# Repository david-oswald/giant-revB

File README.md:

# GIAnt, the Generic Implementation ANalysis Toolkit

This is a fork of the original GIAnt project (www.sourceforge.net/projects/giant/) with a few changes.

## Changes

* The board
	* There is a GIAnt fault only design by David Oswald
	* The FPGA module is updated to `ZTEX USB-FPGA Module 2.04` with `series 2 to series 1 adapter board`

* The FPGA source code
	* Modified from `giant-20111116`
	* The FPGA selection of the project is changed to XC6SLX16
	* IP cores regenerated
	* .ucf file updated to match the new pinout of series 2 module

* The microcontroller source code is updated to fit the new board

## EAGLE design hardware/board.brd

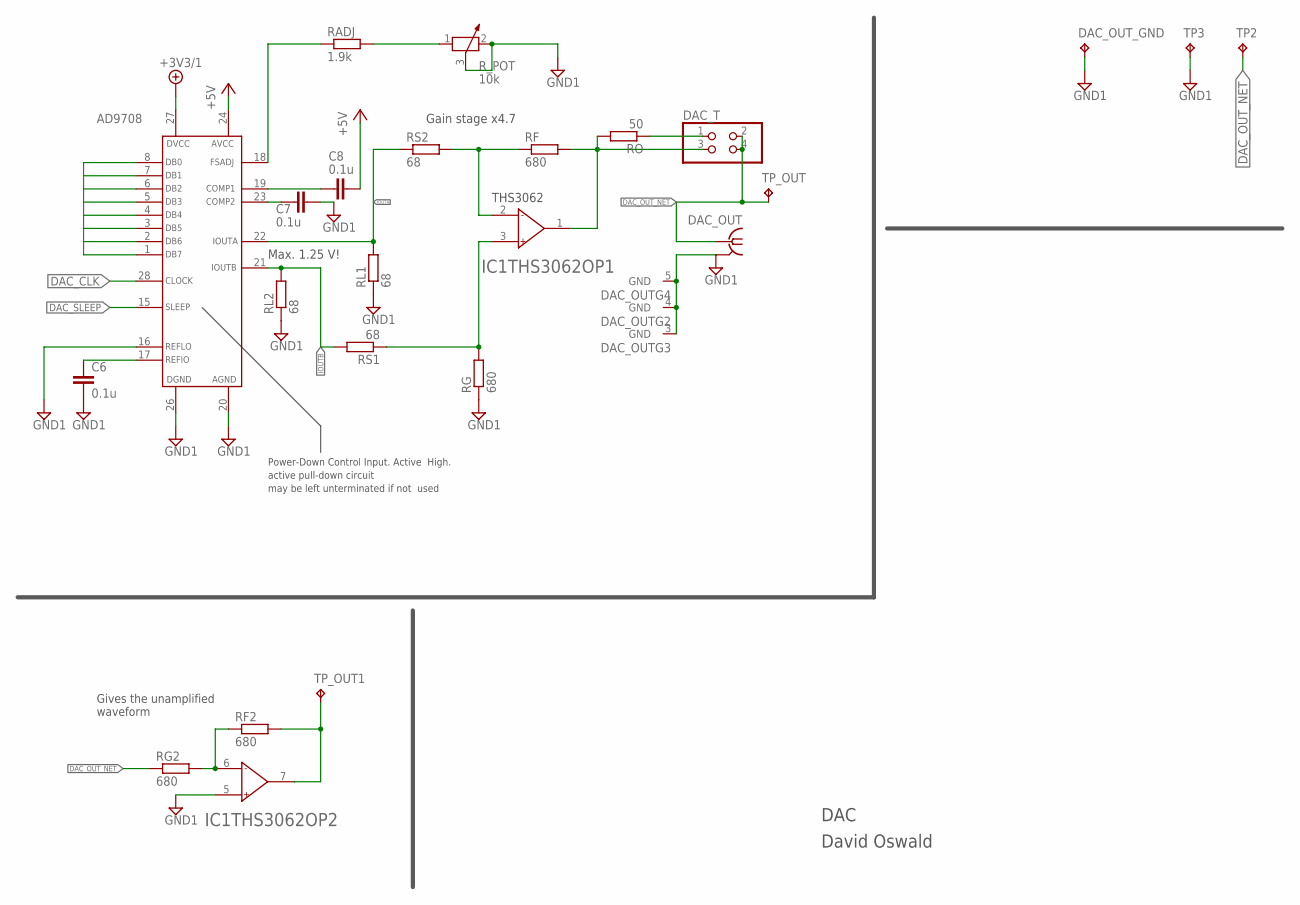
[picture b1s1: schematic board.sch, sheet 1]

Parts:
AD9708: AD7908; SO28W
C6, C7, C8: 0.1u; C0805K
DAC_OUT: BU-SMA-V
DAC_OUT_GND: TPB1,27; B1,27
DAC_T: PINHD-2X2; 2X02
IC1: THS3062; SO08
RADJ: 1.9k; R0805
RF, RF2: 680; R0805
RG, RG2: 680; R0805
RL1, RL2: 68; R0805
RO: 50; R0805
RS1, RS2: 68; R0805
R_POT: 10k; PT-SPIN
TP2, TP3: TPPAD1-13; P1-13
TP_OUT, TP_OUT1: TPB1,27; B1,27

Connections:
+5V: AD9708.24 (AVCC), C8.1; also elsewhere on the board
+5V/1: AD9708.27 (DVCC); also elsewhere on the board
COMP1: AD9708.19 (COMP1), C8.2
COMP2: AD9708.23 (COMP2), C7.1
DAC_CLK: AD9708.28 (CLOCK); also elsewhere on the board
DAC_OUT_NET: DAC_OUT.1, DAC_T.2, DAC_T.4, RG2.1, TP2.TP, TP_OUT.TP
DAC_SLEEP: AD9708.15 (SLEEP)
DB0: AD9708.8 (DB0); also elsewhere on the board
DB1: AD9708.7 (DB1); also elsewhere on the board
DB2: AD9708.6 (DB2); also elsewhere on the board
DB3: AD9708.5 (DB3); also elsewhere on the board
DB4: AD9708.4 (DB4); also elsewhere on the board
DB5: AD9708.3 (DB5); also elsewhere on the board
DB6: AD9708.2 (DB6); also elsewhere on the board
DB7: AD9708.1 (DB7); also elsewhere on the board
FSADJ: AD9708.18 (FSADJ), RADJ.1
GND1: AD9708.16 (REFLO), AD9708.20 (AGND), AD9708.26 (DGND), C6.2, C7.2, DAC_OUT.2 (GND), DAC_OUT.3 (GND), DAC_OUT.4 (GND), DAC_OUT.5 (GND), DAC_OUT_GND.TP, IC1.5 (IN+), RG.1, RL1.1, RL2.1, R_POT.2, R_POT.3, TP3.TP; also elsewhere on the board
IOUTA: AD9708.22 (IOUTA), RL1.2, RS2.1
IOUTB: AD9708.21 (IOUTB), RL2.2, RS1.2
unnamed: IC1.3 (IN+), RG.2, RS1.1
unnamed: IC1.2 (IN-), RF.1, RS2.2
unnamed: DAC_T.3, IC1.1 (OUT), RF.2, RO.2
unnamed: DAC_T.1, RO.1
unnamed: RADJ.2, R_POT.1
unnamed: IC1.6 (IN-), RF2.1, RG2.2
unnamed: IC1.7 (OUT), RF2.2, TP_OUT1.TP
REFIO: AD9708.17 (REFIO), C6.1

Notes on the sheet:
David Oswald
DAC
Max. 1.25 V!
Gain stage x4.7
Power-Down Control Input. Active High.
active pull-down circuit
may be left unterminated if not used
THS3062
Gives the unamplified waveform

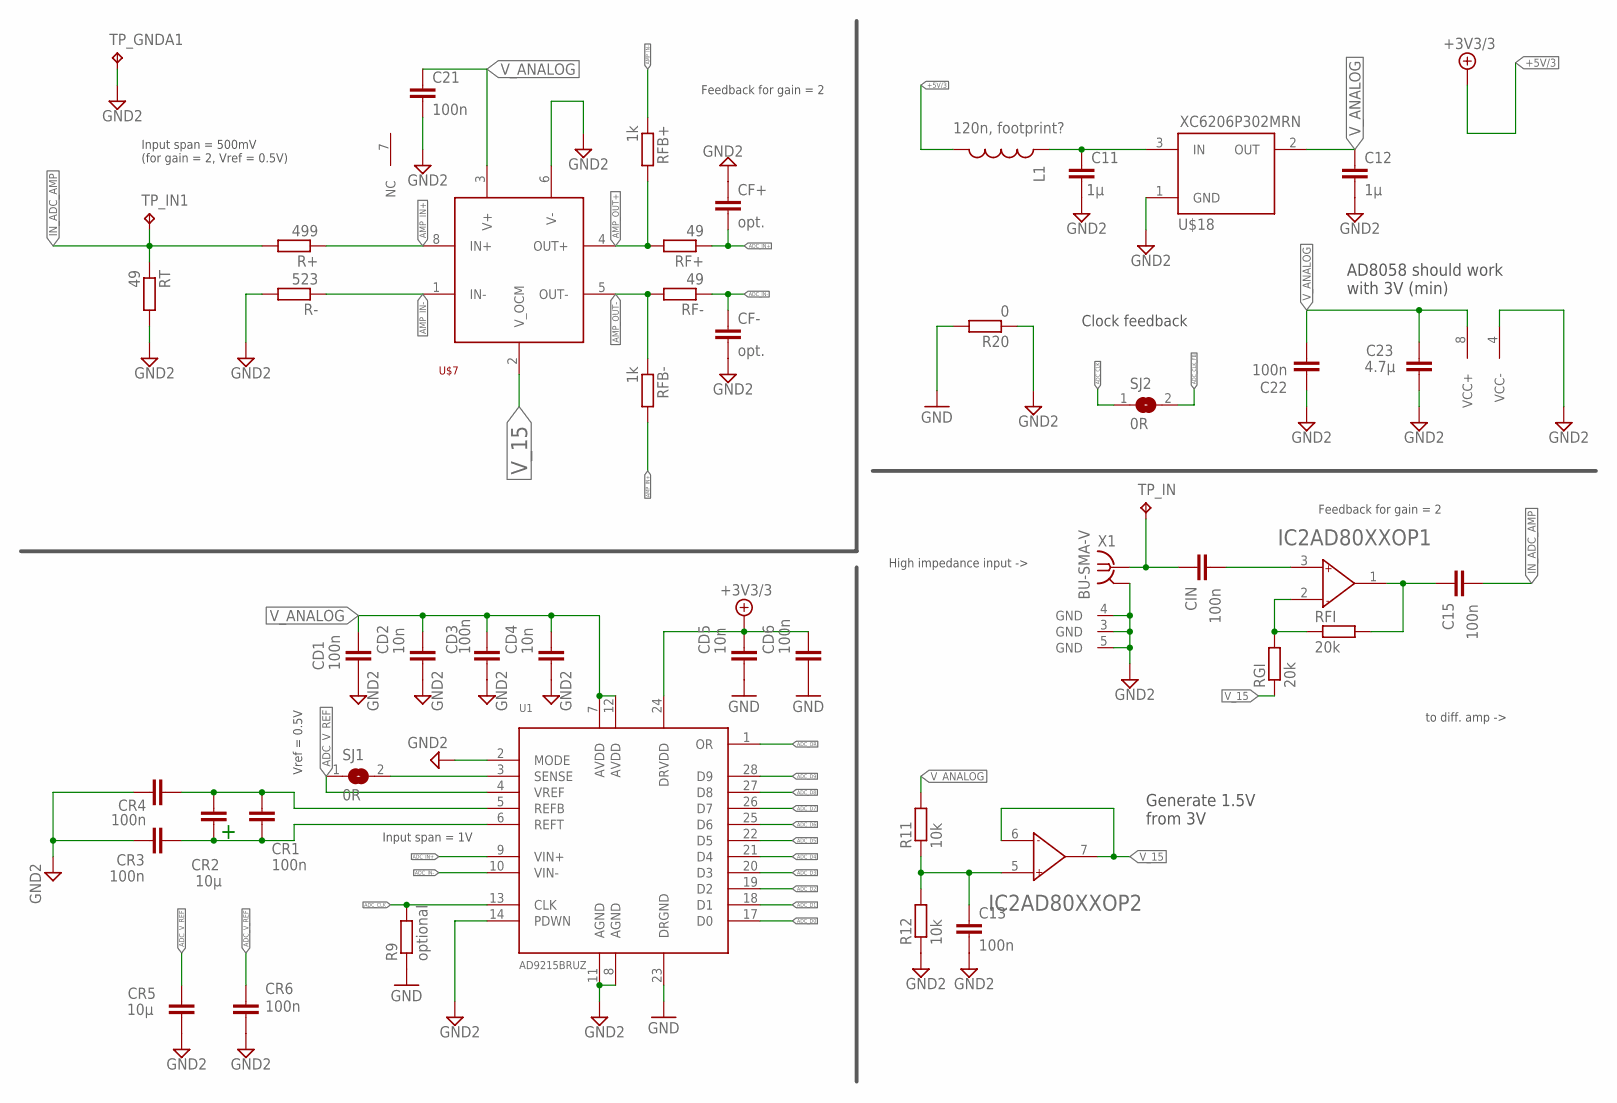
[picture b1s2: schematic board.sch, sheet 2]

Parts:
C11, C12: 1µ; C0805K
C13: 100n; C0805
C15, C21, C22: 100n; C0603
C23: 4.7µ; C0805K
CD1, CD3, CD6: 100n; C0603
CD2, CD4, CD5: 10n; C0603
CF+: opt.; C0603
CF-: opt.; C0603
CIN: 100n; C0603
CR1, CR3, CR4, CR6: 100n; C0603
CR2, CR5: 10µ; C0805K
IC2: AD80XX; SO08
L1: 120n, footprint?; 0805
R9: optional; R0805
R11, R12: 10k; R0805
R20: 0; R0805
R+: 499; R0603
R-: 523; R0603
RF+: 49; R0603
RF-: 49; R0603
RFB+: 1k; R0603
RFB-: 1k; R0603
RFI: 20k; R0603
RGI: 20k; R0603
RT: 49; R0603
SJ1, SJ2: 0R; SJ
TP_GNDA1: TPPAD1-13; P1-13
TP_IN, TP_IN1: TPPAD1-13; P1-13
U1: AD9215BRUZ; TSSOP28
U$7: AD8138; SOIC8
U$18: XC6206P302MRN; SOT23
X1: BU-SMA-V

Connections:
+5V/3: CD5.1, CD6.1, L1.2, U1.24 (DRVDD); also elsewhere on the board
ADC_CLK: R9.2, SJ2.1, U1.13 (CLK); also elsewhere on the board
ADC_CLK_FB: SJ2.2; also elsewhere on the board
ADC_D0: U1.17 (D0); also elsewhere on the board
ADC_D1: U1.18 (D1); also elsewhere on the board
ADC_D2: U1.19 (D2); also elsewhere on the board
ADC_D3: U1.20 (D3); also elsewhere on the board
ADC_D4: U1.21 (D4); also elsewhere on the board
ADC_D5: U1.22 (D5); also elsewhere on the board
ADC_D6: U1.25 (D6); also elsewhere on the board
ADC_D7: U1.26 (D7); also elsewhere on the board
ADC_D8: U1.27 (D8); also elsewhere on the board
ADC_D9: U1.28 (D9); also elsewhere on the board
ADC_IN+: CF+.2, RF+.1, U1.9 (VIN+)
ADC_IN-: CF-.1, RF-.1, U1.10 (VIN-)
ADC_OR: U1.1 (OR); also elsewhere on the board
ADC_V_REF: CR5.2, CR6.2, SJ1.1, U1.4 (VREF)
AMP_IN+: R+.1, RFB-.2, U$7.8 (IN+)
AMP_IN-: R-.1, RFB+.1, U$7.1 (IN-)
AMP_OUT+: RF+.2, RFB+.2, U$7.4 (OUT+)
AMP_OUT-: RF-.2, RFB-.1, U$7.5 (OUT-)
GND: CD5.2, CD6.2, R9.1, R20.2, U1.23 (DRGND); also elsewhere on the board
GND2: C11.2, C12.2, C13.2, C21.2, C22.2, C23.1, CD1.2, CD2.2, CD3.2, CD4.2, CF+.1, CF-.2, CR3.1, CR4.1, CR5.1, CR6.1, R12.1, R20.1, R-.2, RT.2, TP_GNDA1.TP, U1.2 (MODE), U1.8 (AGND), U1.11 (AGND), U1.14 (PDWN), U$7.6 (V-), U$18.1 (GND), X1.2 (GND), X1.3 (GND), X1.4 (GND), X1.5 (GND)
IN_ADC_AMP: C15.2, R+.2, RT.1, TP_IN1.TP
unnamed: C11.1, L1.1, U$18.3 (IN)
unnamed: SJ1.2, U1.3 (SENSE)
unnamed: CR1.2, CR2.2, CR3.2, U1.6 (REFT)
unnamed: CR1.1, CR2.1, CR4.2, U1.5 (REFB)
unnamed: CIN.1, TP_IN.TP, X1.1
unnamed: CIN.2, IC2.3 (IN+)
unnamed: C15.1, IC2.1 (OUT), RFI.2
unnamed: IC2.2 (IN-), RFI.1, RGI.2
OP-: IC2.4 (VCC-)
V_15: IC2.6 (IN-), IC2.7 (OUT), RGI.1, U$7.2 (V_OCM)
V_15_UNBUF: C13.1, IC2.5 (IN+), R11.1, R12.2
V_ANALOG: C12.1, C21.1, C22.1, C23.2, CD1.1, CD2.1, CD3.1, CD4.1, IC2.8 (VCC+), R11.2, U1.7 (AVDD), U1.12 (AVDD), U$7.3 (V+), U$18.2 (OUT)

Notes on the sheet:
Feedback for gain = 2
Clock feedback
AD8058 should work with 3V (min)
Generate 1.5V from 3V
Vref = 0.5V
Input span = 1V
Input span = 500mV (for gain = 2, Vref = 0.5V)
High impedance input ->
to diff. amp ->

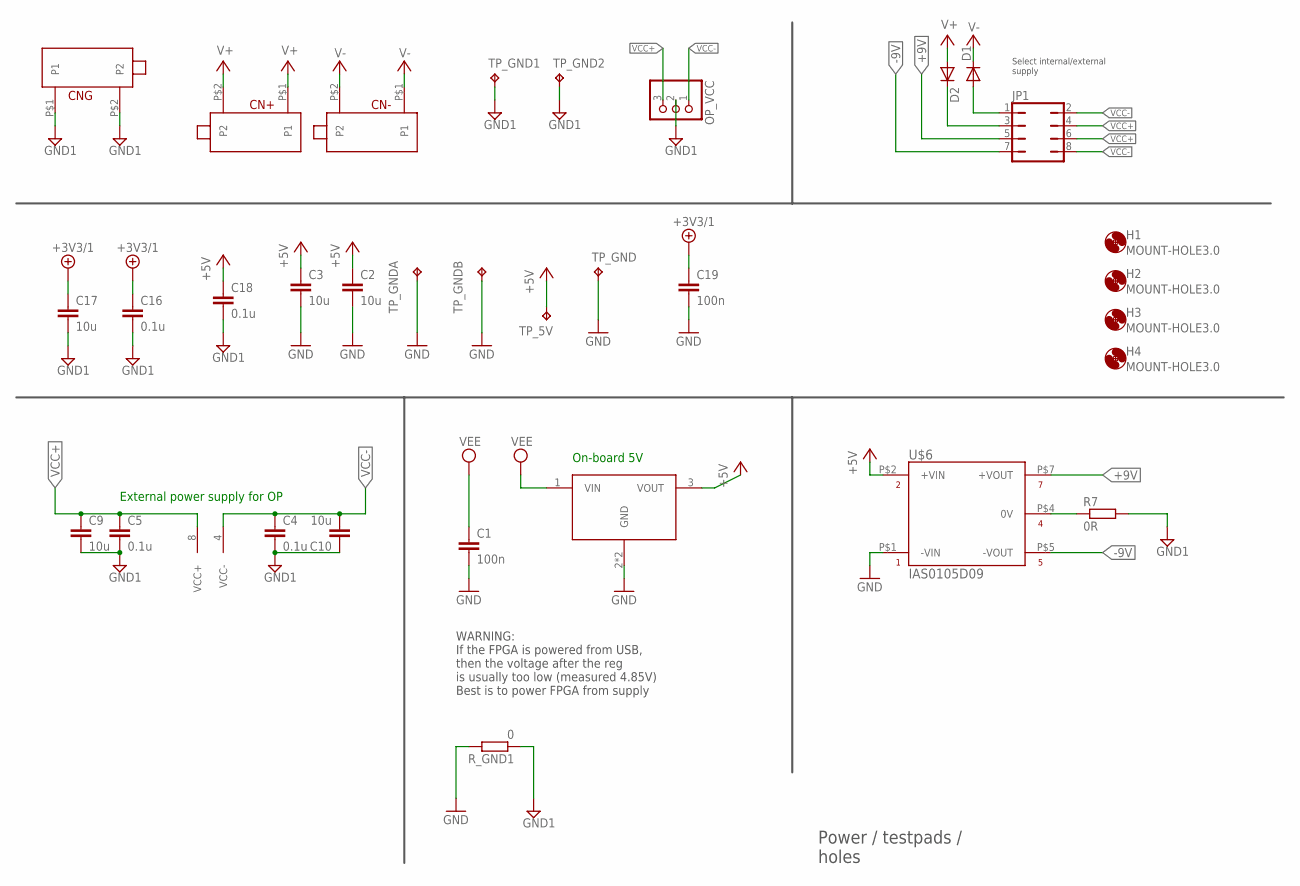
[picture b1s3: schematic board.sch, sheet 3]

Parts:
C1, C19: 100n; C0805K
C2, C3, C9, C10, C17: 10u; C0805K
C4, C5, C16, C18: 0.1u; C0805K
CN+: 24243; 24_243
CN-: 24243; 24_243
CNG: 24243; 24_243
D1, D2: DIODE-SOD123; SOD123
H1, H2, H3, H4: MOUNT-HOLE3.0; 3,0
IC1: THS3062; SO08
JP1: JP4Q
OP_VCC: PINHD-1X3; 1X03
R7: 0R; M0805
R_GND1: 0; R0805
TP_5V: TPB1,27; B1,27
TP_GND, TP_GND1: TPB1,27; B1,27
TP_GND2: TPPAD1-13; P1-13
TP_GNDA: TPPAD1-13; P1-13
TP_GNDB: TPPAD1-13; P1-13
U$1: MIC5209; SOT223-3
U$6: IAS0105D09; SMD-DIP10

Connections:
+5V: C2.1, C3.1, C18.1, TP_5V.TP, U$1.3 (VOUT), U$6.P$2 (+VIN); also elsewhere on the board
+5V/1: C16.1, C17.1, C19.1; also elsewhere on the board
+9V: JP1.5, U$6.P$7 (+VOUT)
-9V: JP1.7, U$6.P$5 (-VOUT)
GND: C1.2, C2.2, C3.2, C19.2, R_GND1.2, TP_GND.TP, TP_GNDA.TP, TP_GNDB.TP, U$1.2 (GND), U$1.4 (GND), U$6.P$1 (-VIN); also elsewhere on the board
GND1: C4.2, C5.2, C9.2, C10.1, C16.2, C17.2, C18.2, CNG.P$1 (P1), CNG.P$2 (P2), OP_VCC.2, R7.2, R_GND1.1, TP_GND1.TP, TP_GND2.TP; also elsewhere on the board
unnamed: R7.1, U$6.P$4 (0V)
unnamed: D2.C, JP1.3
unnamed: D1.A, JP1.1
V+: CN+.P$1 (P1), CN+.P$2 (P2), D2.A
V-: CN-.P$1 (P1), CN-.P$2 (P2), D1.C
VCC+: C5.1, C9.1, IC1.8 (VCC+), JP1.4, JP1.6, OP_VCC.3
VCC-: C4.1, C10.2, IC1.4 (VCC-), JP1.2, JP1.8, OP_VCC.1
VEE: C1.1, U$1.1 (VIN); also elsewhere on the board

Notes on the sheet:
External power supply for OP
Power / testpads / holes
On-board 5V
WARNING: If the FPGA is powered from USB, then the voltage after the reg is usually too low (measured 4.85V) Best is to power FPGA from supply
Select internal/external supply

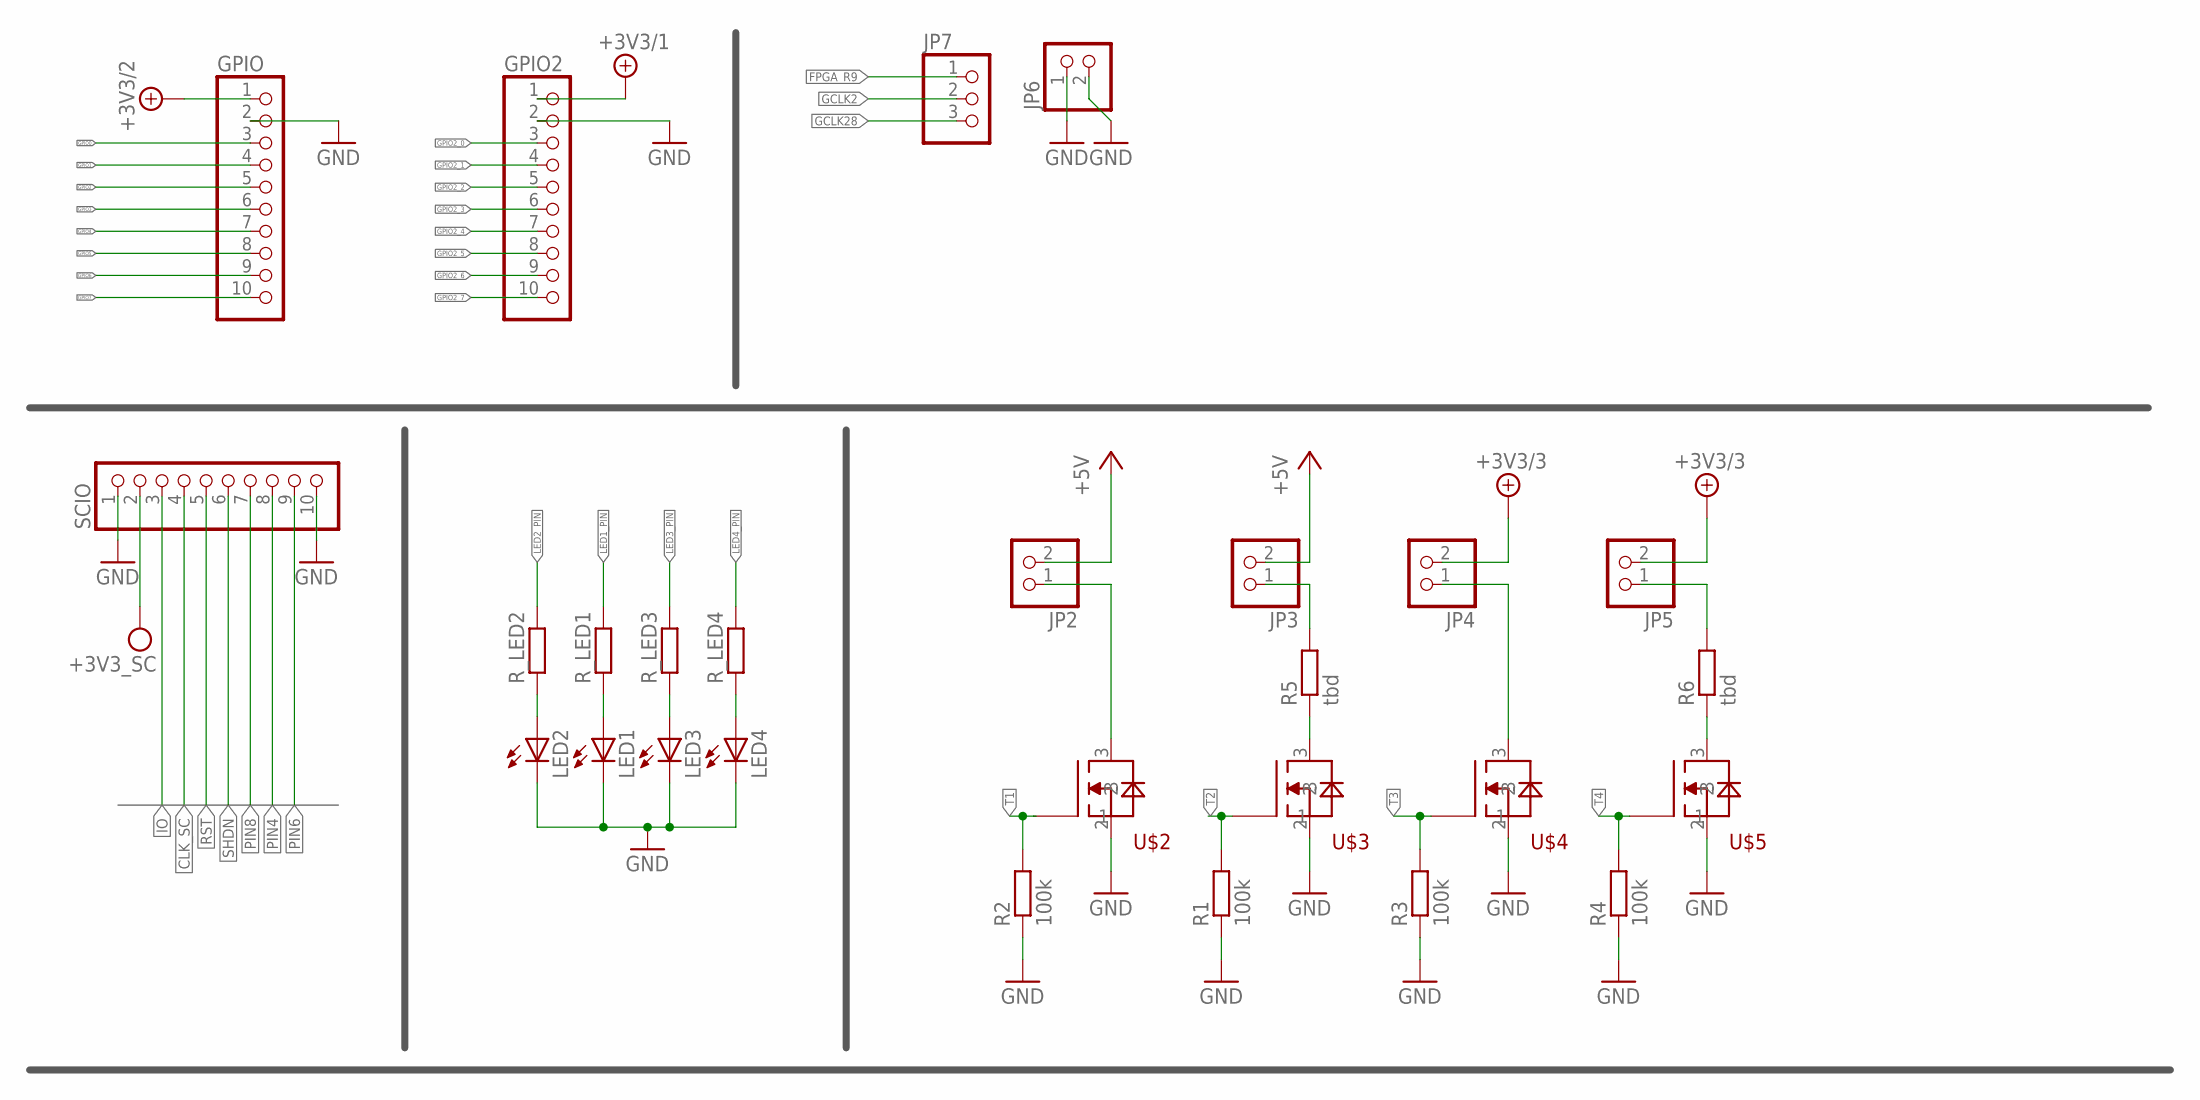
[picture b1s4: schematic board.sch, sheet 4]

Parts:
GPIO, GPIO2: PINHD-1X10; 1X10
JP2, JP3, JP4, JP5, JP6: PINHD-1X2; 1X02
JP7: PINHD-1X3; 1X03
LED1, LED2, LED3, LED4: LEDCHIPLED_0805; CHIPLED_0805
R1, R2, R3, R4: 100k; M0805
R5, R6: tbd; M0805
R_LED1, R_LED2, R_LED3, R_LED4: R-EU_R0805; R0805
SCIO: PINHD-1X10; 1X10
U$2, U$3, U$4, U$5: DMG1012UW; DMG1012UW1-SMT323

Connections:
+5V: JP2.2, JP3.2; also elsewhere on the board
+5V/1: GPIO2.1; also elsewhere on the board
+5V/2: GPIO.1; also elsewhere on the board
+5V/3: JP4.2, JP5.2; also elsewhere on the board
CLK_SC: SCIO.4; also elsewhere on the board
FPGA_R9: JP7.1; also elsewhere on the board
GCLK2: JP7.2; also elsewhere on the board
GCLK28: JP7.3; also elsewhere on the board
GND: GPIO.2, GPIO2.2, JP6.1, JP6.2, LED1.C, LED2.C, LED3.C, LED4.C, R1.1, R2.1, R3.1, R4.1, SCIO.1, SCIO.10, U$2.2, U$3.2, U$4.2, U$5.2; also elsewhere on the board
GPIO0: GPIO.3; also elsewhere on the board
GPIO1: GPIO.4; also elsewhere on the board
GPIO2: GPIO.5; also elsewhere on the board
GPIO2_0: GPIO2.3; also elsewhere on the board
GPIO2_1: GPIO2.4; also elsewhere on the board
GPIO2_2: GPIO2.5; also elsewhere on the board
GPIO2_3: GPIO2.6; also elsewhere on the board
GPIO2_4: GPIO2.7; also elsewhere on the board
GPIO2_5: GPIO2.8; also elsewhere on the board
GPIO2_6: GPIO2.9; also elsewhere on the board
GPIO2_7: GPIO2.10; also elsewhere on the board
GPIO3: GPIO.6; also elsewhere on the board
GPIO4: GPIO.7; also elsewhere on the board
GPIO5: GPIO.8; also elsewhere on the board
GPIO6: GPIO.9; also elsewhere on the board
GPIO7: GPIO.10; also elsewhere on the board
IO: SCIO.3; also elsewhere on the board
LED1_PIN: R_LED1.2; also elsewhere on the board
LED2_PIN: R_LED2.2; also elsewhere on the board
LED3_PIN: R_LED3.2; also elsewhere on the board
LED4_PIN: R_LED4.2; also elsewhere on the board
unnamed: R5.1, U$3.3
unnamed: JP2.1, U$2.3
unnamed: JP3.1, R5.2
unnamed: R6.1, U$5.3
unnamed: JP4.1, U$4.3
unnamed: JP5.1, R6.2
unnamed: LED2.A, R_LED2.1
unnamed: LED1.A, R_LED1.1
unnamed: LED3.A, R_LED3.1
unnamed: LED4.A, R_LED4.1
PIN4: SCIO.8; also elsewhere on the board
PIN6: SCIO.9; also elsewhere on the board
PIN8: SCIO.7; also elsewhere on the board
RST: SCIO.5; also elsewhere on the board
SHDN: SCIO.6; also elsewhere on the board
T1: R2.2, U$2.1; also elsewhere on the board
T2: R1.2, U$3.1; also elsewhere on the board
T3: R3.2, U$4.1; also elsewhere on the board
T4: R4.2, U$5.1; also elsewhere on the board
VPP: SCIO.2; also elsewhere on the board

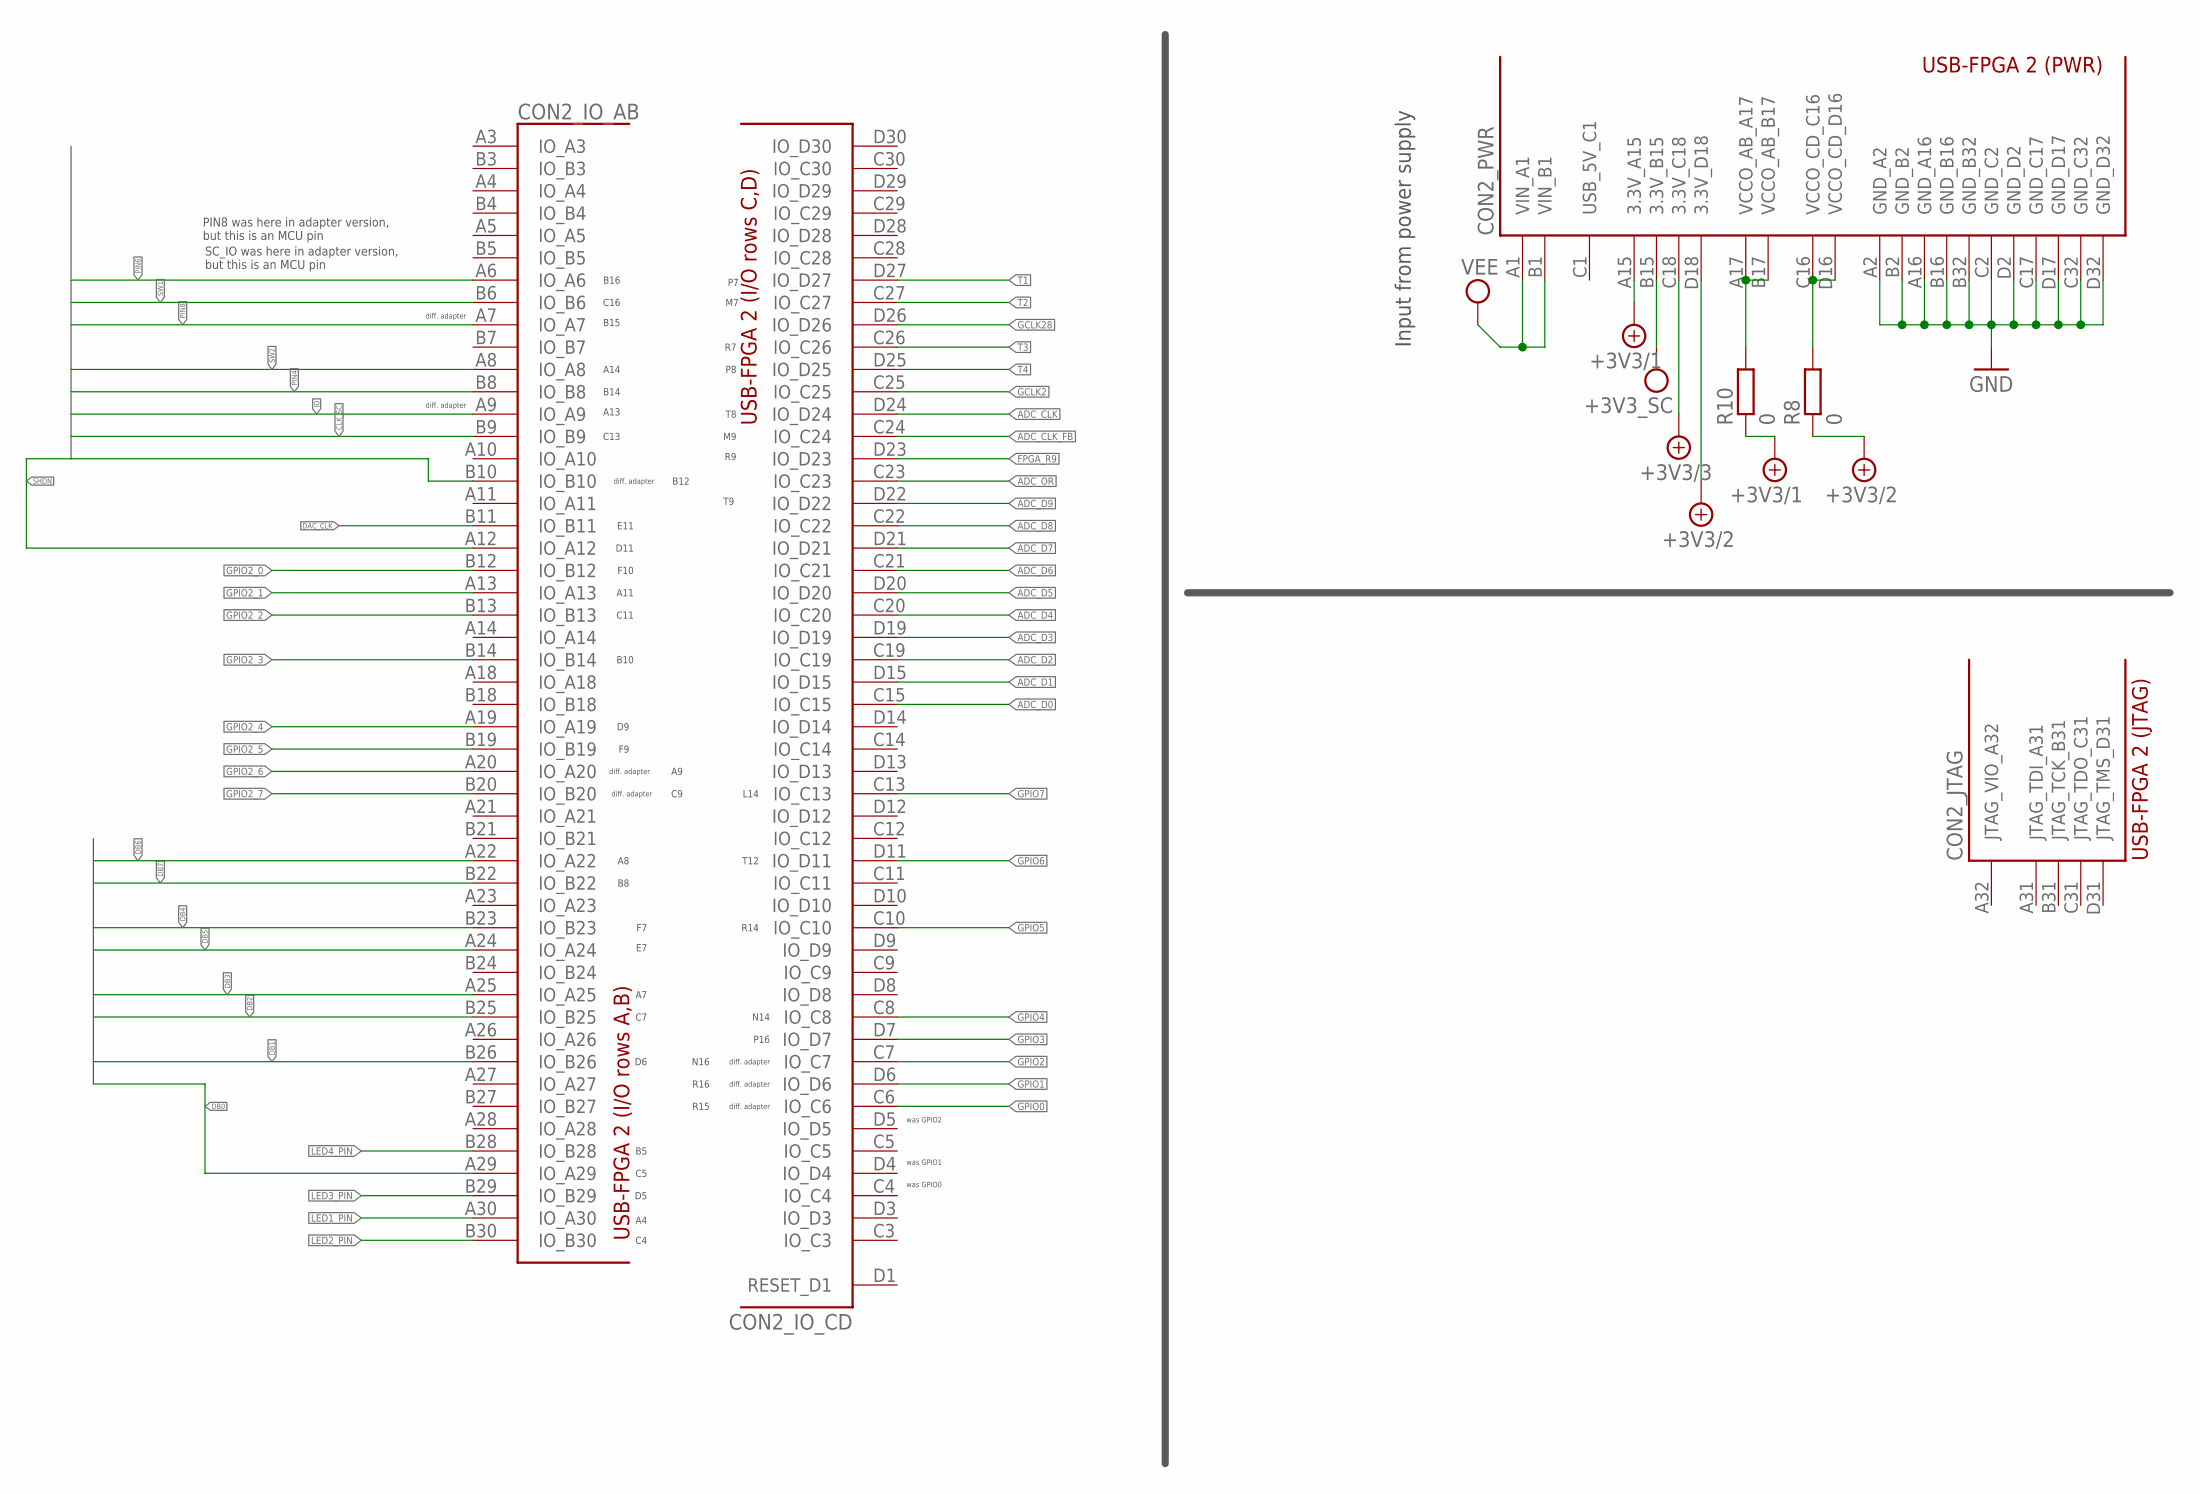
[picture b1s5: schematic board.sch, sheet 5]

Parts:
CON2: USB-FPGA-2THT; USB-FPGA-2-THT
R8, R10: 0; R0805

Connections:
+5V/1: CON2.A15 (3.3V_A15), R10.1; also elsewhere on the board
+5V/2: CON2.D18 (3.3V_D18), R8.1; also elsewhere on the board
+5V/3: CON2.C18 (3.3V_C18); also elsewhere on the board
ADC_CLK: CON2.D24 (IO_D24); also elsewhere on the board
ADC_CLK_FB: CON2.C24 (IO_C24); also elsewhere on the board
ADC_D0: CON2.C15 (IO_C15); also elsewhere on the board
ADC_D1: CON2.D15 (IO_D15); also elsewhere on the board
ADC_D2: CON2.C19 (IO_C19); also elsewhere on the board
ADC_D3: CON2.D19 (IO_D19); also elsewhere on the board
ADC_D4: CON2.C20 (IO_C20); also elsewhere on the board
ADC_D5: CON2.D20 (IO_D20); also elsewhere on the board
ADC_D6: CON2.C21 (IO_C21); also elsewhere on the board
ADC_D7: CON2.D21 (IO_D21); also elsewhere on the board
ADC_D8: CON2.C22 (IO_C22); also elsewhere on the board
ADC_D9: CON2.D22 (IO_D22); also elsewhere on the board
ADC_OR: CON2.C23 (IO_C23); also elsewhere on the board
CLK_SC: CON2.B9 (IO_B9); also elsewhere on the board
DAC_CLK: CON2.B11 (IO_B11); also elsewhere on the board
DB0: CON2.A29 (IO_A29); also elsewhere on the board
DB1: CON2.B26 (IO_B26); also elsewhere on the board
DB2: CON2.B25 (IO_B25); also elsewhere on the board
DB3: CON2.A25 (IO_A25); also elsewhere on the board
DB4: CON2.B23 (IO_B23); also elsewhere on the board
DB5: CON2.A24 (IO_A24); also elsewhere on the board
DB6: CON2.A22 (IO_A22); also elsewhere on the board
DB7: CON2.B22 (IO_B22); also elsewhere on the board
FPGA_R9: CON2.D23 (IO_D23); also elsewhere on the board
GCLK2: CON2.C25 (IO_C25); also elsewhere on the board
GCLK28: CON2.D26 (IO_D26); also elsewhere on the board
GND: CON2.A2 (GND_A2), CON2.A16 (GND_A16), CON2.B2 (GND_B2), CON2.B16 (GND_B16), CON2.B32 (GND_B32), CON2.C2 (GND_C2), CON2.C17 (GND_C17), CON2.C32 (GND_C32), CON2.D2 (GND_D2), CON2.D17 (GND_D17), CON2.D32 (GND_D32); also elsewhere on the board
GPIO0: CON2.C6 (IO_C6); also elsewhere on the board
GPIO1: CON2.D6 (IO_D6); also elsewhere on the board
GPIO2: CON2.C7 (IO_C7); also elsewhere on the board
GPIO2_0: CON2.B12 (IO_B12); also elsewhere on the board
GPIO2_1: CON2.A13 (IO_A13); also elsewhere on the board
GPIO2_2: CON2.B13 (IO_B13); also elsewhere on the board
GPIO2_3: CON2.B14 (IO_B14); also elsewhere on the board
GPIO2_4: CON2.A19 (IO_A19); also elsewhere on the board
GPIO2_5: CON2.B19 (IO_B19); also elsewhere on the board
GPIO2_6: CON2.A20 (IO_A20); also elsewhere on the board
GPIO2_7: CON2.B20 (IO_B20); also elsewhere on the board
GPIO3: CON2.D7 (IO_D7); also elsewhere on the board
GPIO4: CON2.C8 (IO_C8); also elsewhere on the board
GPIO5: CON2.C10 (IO_C10); also elsewhere on the board
GPIO6: CON2.D11 (IO_D11); also elsewhere on the board
GPIO7: CON2.C13 (IO_C13); also elsewhere on the board
IO: CON2.A9 (IO_A9); also elsewhere on the board
LED1_PIN: CON2.A30 (IO_A30); also elsewhere on the board
LED2_PIN: CON2.B30 (IO_B30); also elsewhere on the board
LED3_PIN: CON2.B29 (IO_B29); also elsewhere on the board
LED4_PIN: CON2.B28 (IO_B28); also elsewhere on the board
unnamed: CON2.A17 (VCCO_AB_A17), CON2.B17 (VCCO_AB_B17), R10.2
unnamed: CON2.C16 (VCCO_CD_C16), CON2.D16 (VCCO_CD_D16), R8.2
PIN4: CON2.B8 (IO_B8); also elsewhere on the board
PIN6: CON2.A6 (IO_A6); also elsewhere on the board
PIN8: CON2.A7 (IO_A7); also elsewhere on the board
RST: CON2.B10 (IO_B10); also elsewhere on the board
SHDN: CON2.A12 (IO_A12); also elsewhere on the board
SW1: CON2.B6 (IO_B6)
SW2: CON2.A8 (IO_A8)
T1: CON2.D27 (IO_D27); also elsewhere on the board
T2: CON2.C27 (IO_C27); also elsewhere on the board
T3: CON2.C26 (IO_C26); also elsewhere on the board
T4: CON2.D25 (IO_D25); also elsewhere on the board
VEE: CON2.A1 (VIN_A1), CON2.B1 (VIN_B1); also elsewhere on the board
VPP: CON2.B15 (3.3V_B15); also elsewhere on the board

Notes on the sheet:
Input from power supply
SC_IO was here in adapter version, but this is an MCU pin
diff. adapter
PIN8 was here in adapter version, but this is an MCU pin
was GPIO1
was GPIO0
was GPIO2
B16
C16
B15
A14
B14
A13
C13
B12
E11
D11
F10
A11
C11
B10
R15
R16
N16
P16
N14
R14
T12
L14
